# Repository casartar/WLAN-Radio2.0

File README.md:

# WLAN-Radio2.0

## 1. Komponenten
TBD

## Testaufbau
### SMD Bestückung
Siehe [ibom](https://github.com/casartar/WLAN-Radio2.0/blob/main/Hardware/WLAN-Radio-HAT/bom/ibom.html)
### THT Bestückung

Buchsenleiste an WLAN-Radio-HAT anlöten. Darauf auchten, dass der Stecker gut auf der Platine aufliegt.

Gewinkelte Stiftleisten anlöten.

Aus Gründen für die 5V Spannungsversorgung gerade Stiftleisten verwenden.

Buchsenleiste and LCD anlöten.

Gewinkelte Stifleisten an Verstärkermodul anlöten.

### Testaufbau

* WLAN-Radio-HAT auf Raspberry Pi Zero W stecken.
* LCD anschließen.
* Verstärker anschließen.
* Lautsprecher an Verstärker anstecken.
* Micro-USB-Kabel an das Raspberry Pi anschließen (PWR IN).

## Software-Installation

### Erstellen der SD-Karte für den Raspberry Pi mittels Raspberry Pi Imager

Raspberry Pi Imager installieren - https://www.raspberrypi.com/software/ 

Raspberry Pi Imager ausführen.

Gerät wählen: Raspberry Pi Zero

Os wählen: Raspberry Pi OS (other)

Raspberry Pi OS (Legacy) Lite

SD-Karte wählen.

Next

Einstellungen bearbeiten.

* Hostname: individuell benennen.
* Benutzer: "pi"
* Passwort: "raspberry"
* SSID: geheim
* Passwort: geheim

Im Reiter "Dienste" kann man auch gerne seinen Public Key hinterlegen, muss aber nicht sein.

Im Reiter "Dienste" SSH aktivieren und "Passwort zur Authentifizierung verwenden" auswählen. Wer weiß was er tut, kann man auch gerne seinen Public Key hinterlegen, muss aber nicht sein.

Speichern und Ja wählen und mit Ja bestätigen

SD-Karte wird beschrieben.

SD-Karte ist fertig beschrieben.

SD-Karte in Pi einstecken und Micro-USB-Kabel an Laptop anschließen.
  
### Der erste Start des Pi dauert u.U. mehrere Minuten

### System aktualisieren
IP Adresse herausfinden

Verbinden per ssh, user: pi; passwort wie oben konfiguriert.
Der Befehl funktioniert unter Linux und unter Window in der PowerShell

```
ssh pi@xxx.xxx.xxx.xxx

sudo apt update
sudo apt upgrade
```

### GIT installieren und WLAN-Radio2.0 clonen

```
sudo apt install git
sudo git clone https://github.com/casartar/WLAN-Radio2.0.git
```

### LCD Komponenten installieren und Testen

```
sudo apt install i2c-tools
sudo apt install python3-pip
sudo apt install python3-smbus
pip install RPLCD
```
Wenn pip einen Fehler ausgibt noch mal versuchen mit:
```
pip install RPLCD --break-system-packages
```

/boot/config.txt anpassen mit

```
sudo nano /boot/config.txt
```

Parameter: **dtparam=i2c_arm=on** einkommentieren

Speichern mit Strg+O, Enter und Schließen mit Strg+X.

Neustart

```
sudo reboot
```

Verbinden per ssh

```
sudo i2cdetect -y 1
cd ~/WLAN-Radio2.0/Software
python3 lcd_test.py
```

Auf dem LCD sollte jetzt **"WLAN Radio"** und **"1234567890abcdef"** angezeigt werden.

### Audio Komponenten installieren und Testen

/boot/config.txt anpassen mit

```
sudo nano /boot/config.txt
```

Am Ende der Datei hinzufügen: **dtoverlay=hifiberry-dac**
Zeile auskommentieren (Raute vorne dran) **#dtparam=audio=on**
Zeile auskommentieren (Raute vorne dran)  **#dtoverlay=vc4-kms-v3d**

Speichern mit Strg+O, Enter und Schließen mit Strg+X.

Neustart

```
sudo reboot
```

Verbinden per ssh

Testen mit:

```
speaker-test -t wav -c 2
```

Es sollte "Front Left" und "Front Right" aus den entsprechenden Lautsprechern ertönen.

Mit Strg + C kann die Ausgabe abbrechen.

### MPD und MPC einrichten (Music Player Daemon, Music Player Client)

```
sudo apt install mpd
sudo apt install mpc
```

/etc/mpd.conf anpassen mit

```
sudo nano /etc/mpd.conf
```

Zeile ändern von
```
playlist_directory   /var/lib/mpd/playlists
```
in
```
playlist_directory   /home/pi/Playlists/
```

und 

```
audio_output {
#       type            "alsa"
#       name            "My ALSA Device"
#       device          "hw:0,0"        # optional
#       mixer_type      "hardware"      # optional
#       mixer_device    "default"       # optional
#       mixer_control   "PCM"           # optional
#       mixer_index     "0"             # optional
}
```
ändern in 

```
audio_output { 
        type            "alsa" 
        name            "sysdefault:CARD=sndrpihifiberry" 
        mixer_type      "software" 
}
```

Speichern mit Strg+O, Enter und Schließen mit Strg+X.

Das Verzeichnis anlegen: 
```
mkdir ~/Playlists
```

Default Playlist aus dem Repo in dieses Verzeichnis kopieren: 

```
cp ~/WLAN-Radio2.0/Playlist/Playlist.m3u Playlists/
```

mpd.service neu starten: 
```
sudo systemctl restart mpd
```
Testen ob Radio abgespielt wird
```
mpc load Playlist
mpc play
mpc next
mpc status
mpc pause
```
Wenn nach mpc load P Playlist nicht autovervollständigt wird, muss evtl. in der mpd.conf der User von mpd zu pi geändert werden.

MPD Library installieren
```
sudo apt install python3-mpd
```
MPD Test Script ausführen
```
cd ~/WLAN-Radio2.0/Software
python3 mpd_test.py
```

Es sollte ein Sender abgespielt werden.

Mit Strg + C wird der test beendet.

### Radio Testen

```
cd ~/WLAN-Radio2.0/Software
python3 radio_test.py
```

Mit der Pinzette die beiden Pins für Next respektive Previous kurzschließen und prüfen, ob ein anderer Sender abgespielt wird.

### Weitere WLAN-Zugangsdaten hinzufügen

```
sudo nano /etc/wpa_supplicant/wpa_supplicant.conf
```
Die konfiguration sollte in etwa so aussehen:

```
ctrl_interface=DIR=/var/run/wpa_supplicant GROUP=netdev
update_config=1

network={
        ssid="HierKönnteIhreSsidStehen"
        psk=e04000a6ccb88f7ac28bd18ed807fdb820ac8524dbc6f50d4bfe2d788c3609fd
}
```

Das muss erweitert werden zu:

```
ctrl_interface=DIR=/var/run/wpa_supplicant GROUP=netdev
update_config=1

network={
        ssid="HierKönnteIhreSsidStehen"
        psk=e04000a6ccb88f7ac28bd18ed807fdb820ac8524dbc6f50d4bfe2d788c3609fd
}
network={
        ssid="AndereSsid"
        psk="pazzzW0rd"
}
```

Speichern mit Strg+O, Enter und Schließen mit Strg+X.

### Autostart

```
sudo cp ~/WLAN-Radio2.0/Config/wlan-radio.service /etc/systemd/system/
sudo chmod 640 /etc/systemd/system/wlan-radio.service
systemctl status wlan-radio
sudo systemctl daemon-reload
sudo systemctl enable wlan-radio
sudo systemctl start wlan-radio
sudo systemctl status wlan-radio
```

## Gehäuse Lasern

Benötigt wird die Datei Case_with_custom_cutouts_6mm.svg

Das Gehäuse wird aus Buche Sperrholzplatten 6mm gelasert. 
Startingpoint sind 80% Leistung und 20 mm/s Geschwindigkeit.

Nach dem Lasern sollten die Schnittkanten mit Schmiergelpapier bearbeitet werden, da das Holz sehr nach verbrannt riecht.

Ob man das Holz weiter bearbeiten, also einölen oder lackieren möchte, darf jeder selbst entscheiden.

## Fräsarbeiten

Die Bedienelemente müssen im Holz versenkt werden, da die Gewinde für 6 mm Holz zu kurz sind.
Für die Vertiefungen wird mit der Oberfräse 3 mm abgefäst.

Wo gefäst werden muss, ist in der Datei Deepenings.svg rot markiert.

ACHTUNG! Die Zeichung ist die Sicht von Außen auf das Radio, die Vertiefungen sind aber innen. Beim Display muss also gespiegelt ausgefräßt werden.

Am besten steckt man die Bauteile in die Aussparungen und zeichnet mit dem Bleistift an, wo gefräßt werden soll.

## Einbau der Elektronik

### Rückwand (USB-C + Pi)
Vor dem einbau der USB-C Buchse werden an die Leitungen Dupont Buchsen gecrimpt.

Um den Pi zu montieren, müssen von außen vier Zylinderkopfschrauben M2,5 mit Länge 8 mm gesteckt werden.
Von innen werden Stehbolzen M2,5 (Länge relativ egal) mit Innen- und Außenewinde auf die Schrauben augeschraubt. Darauf wird der Pi gesteckt. Dann werden wieder vier Stehbolte mit Innen und Außengewinde aufgeschraubt. Länge 11 mm. Dann kommt der HAT und M2,5 Muttern.

### Deckel

An die beiden Taster werden zweipolige Stiftleisten gelötet und dann verschraubt.

Beim Schalter werden an zwei benachbarte Kontakt je eine zweipolige Stiftleiste gelötet.

### Front

Vorne werden die Lautsprecher mit 8 M5 Zylinderkopfschrauben mit Länge 10 mm und entsprechenden Muttern befestigt.

Für das LCD werden 4 M3 Zylinderkopfschrauben mit Länge 12 mm und entsprechende Muttern benötigt.

Der Verstärker wird mit den beiligenden Utensilien befestigt.

## Zusammenleimen

Man benutze viele viele Schraubzwingen und sanfte Gewalt beim Zusammenstecken.

Der Boden wird nicht verleimt, sondern nur gesteckt. Sollte er nicht halten, muss man sich was schlaues überlegen, dass er es doch tut.

## Verkabelung

Wenn alles mit rechten Dingen zugegangen ist, sollte jetzt alles mit ordinären Jumperkabeln zu verbinden sein. 

1. Die gecrimpten Buchsen an der USB-C buchse werden auf die Spannungsversorgungspins auf dem HAT gesteckt.
2. Der mit 5V markierte Pin des LCD-Anschlusses wird mit einem Pin am An/Aus-Schalter verbunden.
3. Vom An/Ausschalter werden zwei weitere Jumperkabel (vom anderen Anschluss) an das LCD und den Verstärker geführt.
4. Je zwei Leitungen werden für die Taster benötigt.
5. Den Rest der Verkabelung für LCD und Verstärker, wie im Testaufbau.

Wenn man jetzt das Netzteil einsteckt, sollte nach eineiger Zeit das Radio ertönen.

## Senderliste bearbeiten

Per SSH verbinden:

```
ssh pi@xxx.xxx.xxx.xxx
cd ~/Playlists
nano Playlist.m3u
```

Hier neue Webstreams hinzufügen.

https://streamurl.link/ scheint eine ganz gute Quelle für URLs zu sein.

Speichern mit Strg+O, Enter und Schließen mit Strg+X.

Das WLAN-Radio neu starten. Dabei wird die Playlist neu eingelesen.

```
sudo systemctl restart wlan-radio
```

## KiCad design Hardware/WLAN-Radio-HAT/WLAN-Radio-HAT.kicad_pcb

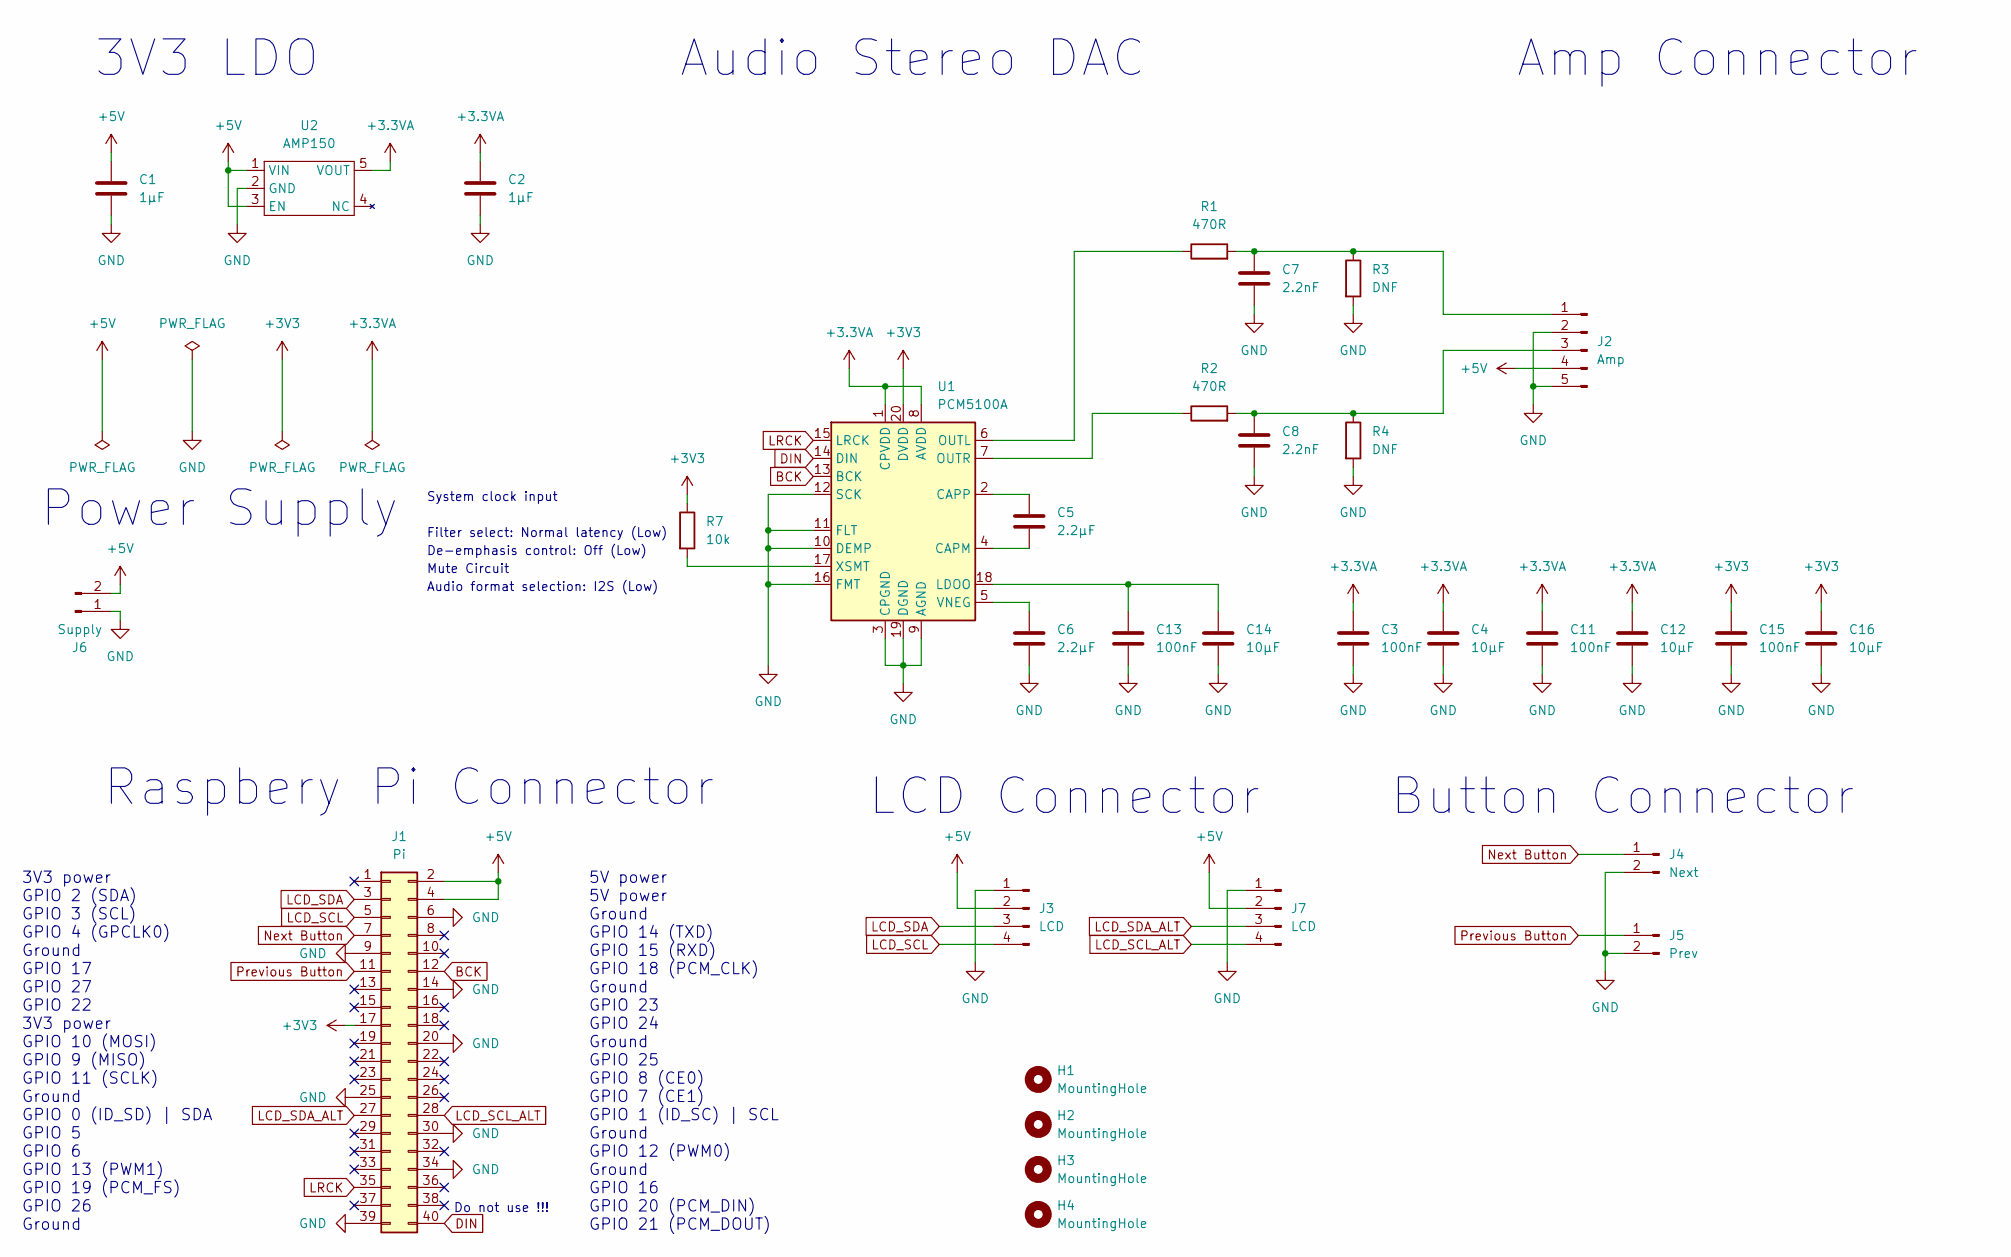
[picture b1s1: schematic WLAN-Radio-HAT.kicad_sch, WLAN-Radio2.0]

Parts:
C1, C2: 1µF; C_0805_2012Metric
C3, C11, C13, C15: 100nF; C_0805_2012Metric
C4, C12, C14, C16: 10µF; C_0805_2012Metric
C5, C6: 2.2µF; C_0805_2012Metric
C7, C8: 2.2nF; C_0805_2012Metric
H1, H2, H3, H4: MountingHole; MountingHole_2.7mm_M2.5
J1: Pi; PinSocket_2x20_P2.54mm_Vertical
J2: Amp; PinHeader_1x05_P2.54mm_Horizontal
J3: LCD; PinHeader_1x04_P2.54mm_Horizontal
J4: Next; PinHeader_1x02_P2.54mm_Horizontal
J5: Prev; PinHeader_1x02_P2.54mm_Horizontal
J6: Supply; PinHeader_1x02_P2.54mm_Horizontal
J7: LCD; PinHeader_1x04_P2.54mm_Vertical
R1, R2: 470R; R_0805_2012Metric
R3, R4: DNF; R_0805_2012Metric
R7: 10k; R_0805_2012Metric
U1: PCM5100A; TSSOP-20_4.4x6.5mm_P0.65mm
U2: AMP150; TSOT-23-5

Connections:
+3.3VA: C2.1, C3.1, C4.1, C11.1, C12.1, U1.1 (CPVDD), U1.8 (AVDD), U2.5 (VOUT)
+3V3: C15.1, C16.1, J1.17, R7.1, U1.20 (DVDD)
+5V: C1.1, J1.2, J1.4, J2.4, J3.2, J6.2, J7.2, U2.1 (VIN), U2.3 (EN)
BCK: J1.12, U1.13 (BCK)
DIN: J1.40, U1.14 (DIN)
GND: C1.2, C2.2, C3.2, C4.2, C6.2, C7.2, C8.2, C11.2, C12.2, C13.2, C14.2, C15.2, C16.2, J1.6, J1.9, J1.14, J1.20, J1.25, J1.30, J1.34, J1.39, J2.2, J2.5, J3.1, J4.2, J5.2, J6.1, J7.1, R3.2, R4.2, U1.3 (CPGND), U1.9 (AGND), U1.10 (DEMP), U1.11 (FLT), U1.12 (SCK), U1.16 (FMT), U1.19 (DGND), U2.2 (GND)
LCD_SCL: J1.5, J3.4
LCD_SCL_ALT: J1.28, J7.4
LCD_SDA: J1.3, J3.3
LCD_SDA_ALT: J1.27, J7.3
LRCK: J1.35, U1.15 (LRCK)
unnamed: C7.1, J2.1, R1.2, R3.1
unnamed: C8.1, J2.3, R2.2, R4.1
unnamed: C5.2, U1.4 (CAPM)
unnamed: C5.1, U1.2 (CAPP)
unnamed: C13.1, C14.1, U1.18 (LDOO)
unnamed: R1.1, U1.6 (OUTL)
unnamed: R2.1, U1.7 (OUTR)
unnamed: C6.1, U1.5 (VNEG)
unnamed: R7.2, U1.17 (XSMT)
Next Button: J1.7, J4.1
Previous Button: J1.11, J5.1

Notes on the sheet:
Mute Circuit
De-emphasis control: Off (Low)
Do not use !!!
Filter select: Normal latency (Low)
5V power 5V power Ground GPIO 14 (TXD) GPIO 15 (RXD) GPIO 18 (PCM_CLK) Ground GPIO 23 GPIO 24 Ground GPIO 25 GPIO 8 (CE0) GPIO 7 (CE1) GPIO 1 (ID_SC) | SCL Ground GPIO 12 (PWM0) Ground GPIO 16 GPIO 20 (PCM_DIN) GPIO 21 (PCM_DOUT)
3V3 LDO
LCD Connector
Power Supply
Audio format selection: I2S (Low)
3V3 power GPIO 2 (SDA) GPIO 3 (SCL) GPIO 4 (GPCLK0) Ground GPIO 17 GPIO 27 GPIO 22 3V3 power GPIO 10 (MOSI) GPIO 9 (MISO) GPIO 11 (SCLK) Ground GPIO 0 (ID_SD) | SDA GPIO 5 GPIO 6 GPIO 13 (PWM1) GPIO 19 (PCM_FS) GPIO 26 Ground
Amp Connector
Audio Stereo DAC
System clock input
Raspbery Pi Connector
Button Connector

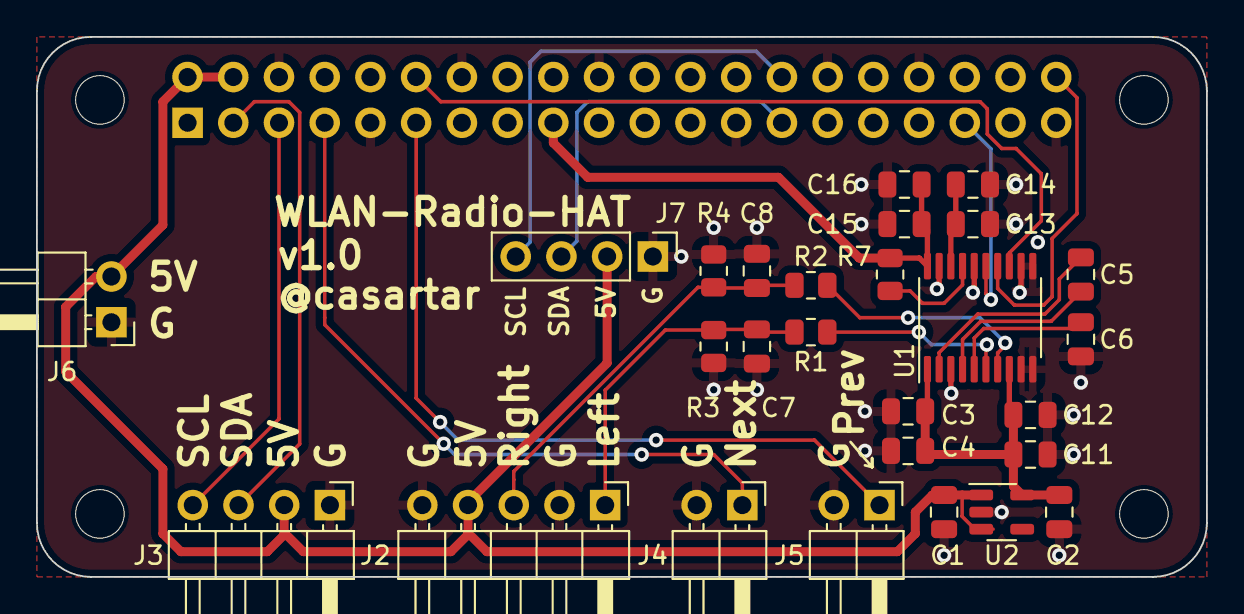
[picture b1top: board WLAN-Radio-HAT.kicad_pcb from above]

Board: 2 copper layers, 65.0 x 30.0 mm, 32 parts (1 on the bottom side), 22 nets.

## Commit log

2023-11-01 mpd loops through playlist with buttons
2023-11-01 some kind of works now
2023-11-02 add test scripts
2023-11-02 add datasheets
2023-11-02 add pcb
2023-11-03 removed unnecessary filter components
2023-11-03 add alternate LCD connector and use better 3v3 supply pin
2023-11-03 drc corrections
2023-11-05 add BasedBox.svg
2023-11-05 add case drawing
2023-11-05 update affinity file
2023-11-08 svg for different wood width
2023-11-09 add hole for on off switch
2023-11-12 add bom
2023-11-12 add gerber
2023-11-12 add first playlist
2023-11-12 Update README.md, Install Infos
2023-11-12 Update README.md, Formatierung
2023-11-19 change playlist name
2023-11-19 add systemd service unit file
2023-11-19 add ibom
2023-11-19 update systemd service unit file
2023-11-20 update case svg and add deepenings
2023-11-21 update readme with sd card preparation screenshots
2023-11-25 add second wifi
2023-11-25 add autostart description and ibom
2023-11-25 add more README stuff
2023-11-29 readme correction
2023-12-01 fix ssh enable in readme
2023-12-01 remove htg
2023-12-01 add configure playlist to readme
2023-12-01 fix wpa_supplicant typo in readme
2023-12-01 correction exit nano
2023-12-01 restart script after playlist modification added to readme
2023-12-01 add stream url tu readme
2023-12-03 size of screws added to readme
2024-01-29 initial commit for esp32 firmware
